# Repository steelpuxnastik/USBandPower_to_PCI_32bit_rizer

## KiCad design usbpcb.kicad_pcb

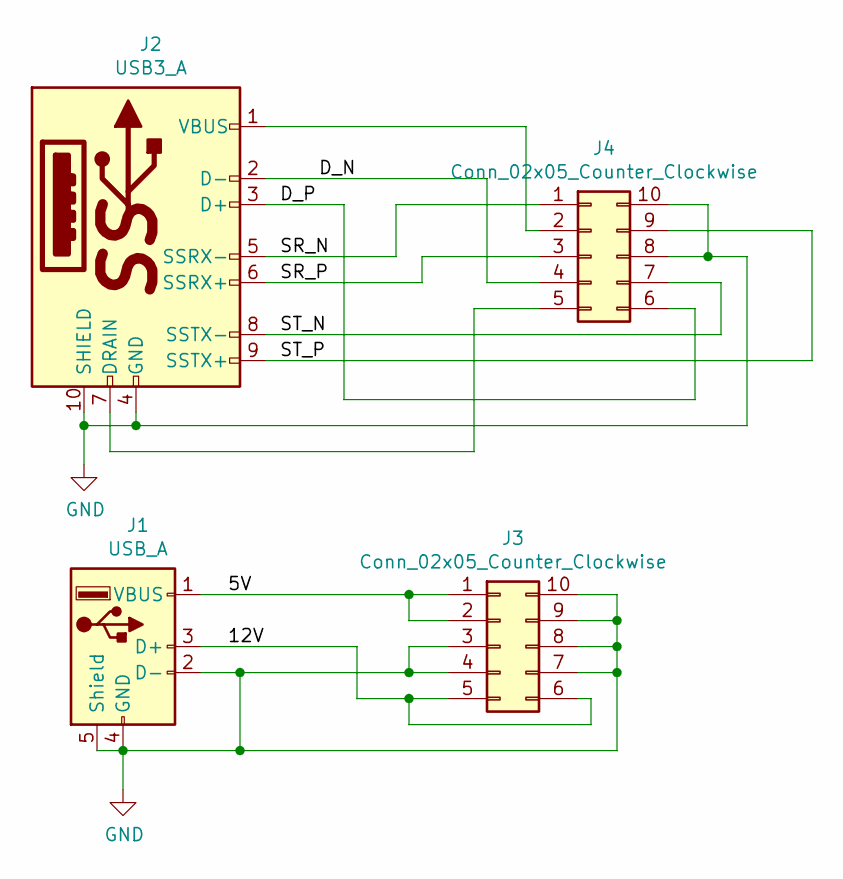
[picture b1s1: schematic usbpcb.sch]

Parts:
J1: USB_A; USB_A_MOTHER
J2: USB3_A; USB3_A_MOTHER
J3, J4: Conn_02x05_Counter_Clockwise; PinHeader_2x05_P2.54mm_Horizontal

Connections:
/5V: J1.1 (VBUS), J3.1, J3.2
/12V: J1.3 (D+), J3.5, J3.6
/D_N: J2.2 (D-), J4.4
/D_P: J2.3 (D+), J4.6
/SR_N: J2.5 (SSRX-), J4.1
/SR_P: J2.6 (SSRX+), J4.3
/ST_N: J2.8 (SSTX-), J4.7
/ST_P: J2.9 (SSTX+), J4.9
GND: J1.2 (D-), J1.4 (GND), J1.5 (Shield), J2.4 (GND), J2.10 (SHIELD), J3.3, J3.4, J3.7, J3.8, J3.9, J3.10, J4.8, J4.10
unnamed: J2.1 (VBUS), J4.2
unnamed: J2.7 (DRAIN), J4.5

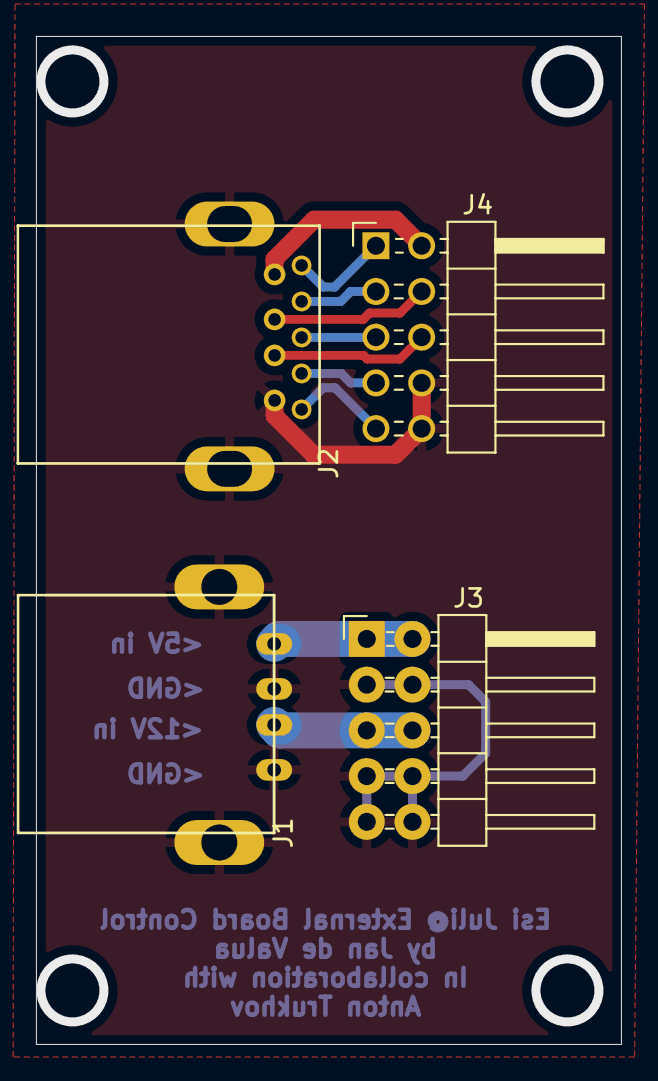
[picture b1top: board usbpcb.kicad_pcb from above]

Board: 2 copper layers, 32.5 x 56.0 mm, 4 parts (0 on the bottom side), 11 nets.

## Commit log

2019-12-14 Alternative variant of location and routing traces
    Alternative variant of location and routing traces, because first try of connection was failed and it's still needs to be verified, what was the reason: bad cable. bad soldiering or PCB design errors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
2021-09-13 update after fail
